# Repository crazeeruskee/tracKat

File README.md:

# tracKat
A Distributed BLE Sensor Network For Tracking Pet Eating Habits

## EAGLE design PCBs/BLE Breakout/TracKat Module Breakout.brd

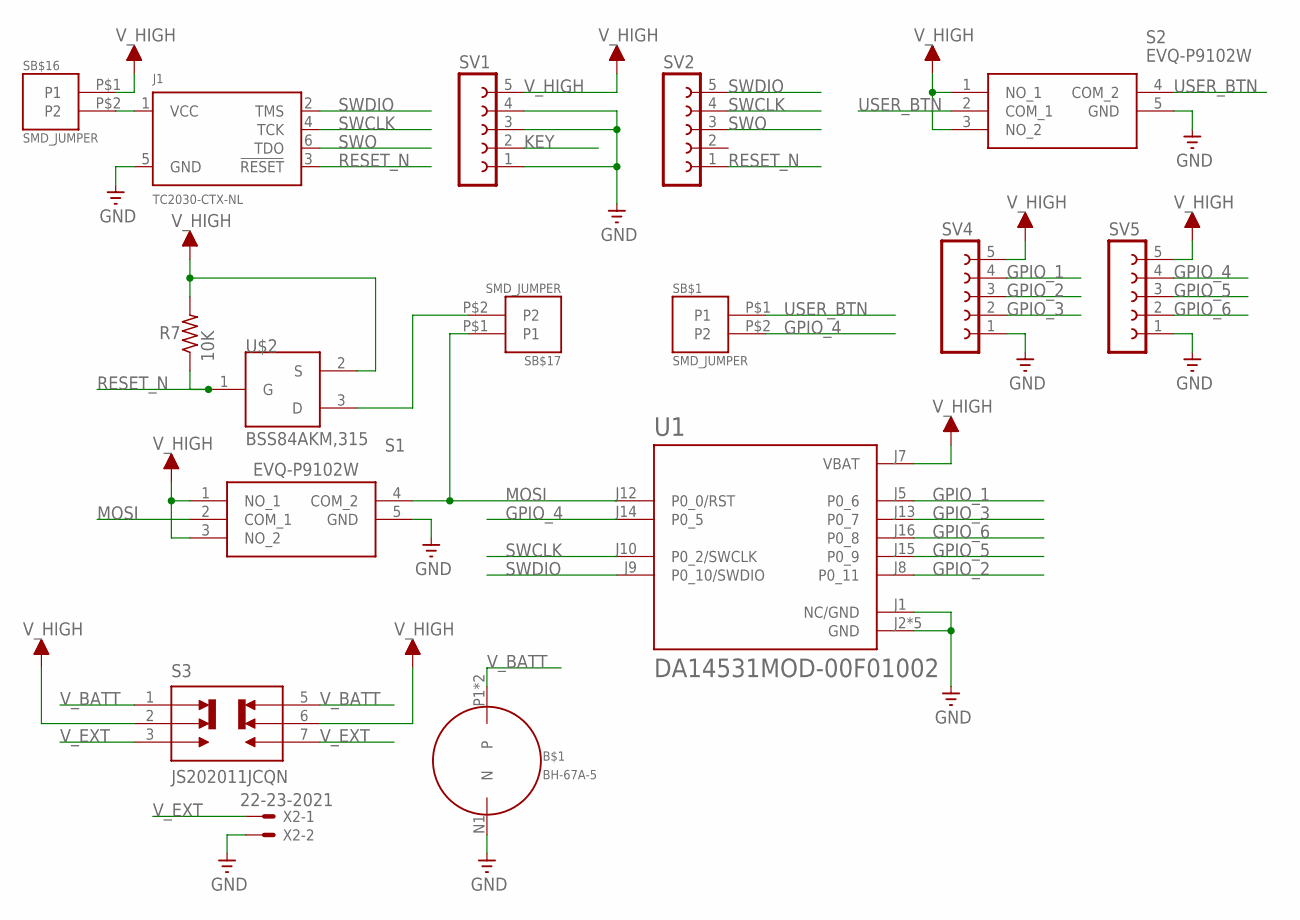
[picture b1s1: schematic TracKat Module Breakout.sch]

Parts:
B$1: BH-67A-5
J1: TC2030-CTX-NL; TC2030-IDC-NL
R7: 10K; R0603
S1, S2: EVQ-P9102W; EVQP9102W
S3: JS202011JCQN; SW_JS202011JCQN
SB$1, SB$16, SB$17: SMD_JUMPER
SV1, SV2, SV4, SV5: FE05-1
U1: DA14531MOD-00F01002; XCVR_DA14531MOD-00F01002
U$2: BSS84AKM,315; DFN985X585X50-3N
X2: 22-23-2021

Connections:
GND: B$1.N1 (N), J1.5 (GND), S1.5 (GND), S2.5 (GND), SV4.1, SV5.1, U1.J1 (NC/GND), U1.J2 (GND), U1.J3 (GND), U1.J4 (GND), U1.J6 (GND), U1.J11 (GND), X2.2
GPIO_1: SV4.4, U1.J5 (P0_6)
GPIO_2: SV4.3, U1.J8 (P0_11)
GPIO_3: SV4.2, U1.J13 (P0_7)
GPIO_4: SB$1.P$2 (P2), SV5.4, U1.J14 (P0_5)
GPIO_5: SV5.3, U1.J15 (P0_9)
GPIO_6: SV5.2, U1.J16 (P0_8)
KEY: SV1.2
MOSI: S1.2 (COM_1), S1.4 (COM_2), SB$17.P$1 (P1), U1.J12 (P0_0/RST)
unnamed: SV1.1, SV1.3, SV1.4
unnamed: J1.1 (VCC), SB$16.P$2 (P2)
unnamed: SB$17.P$2 (P2), U$2.3 (D)
RESET_N: J1.3 (!RESET), R7.1, SV2.1, U$2.1 (G)
SWCLK: J1.4 (TCK), SV2.4, U1.J10 (P0_2/SWCLK)
SWDIO: J1.2 (TMS), SV2.5, U1.J9 (P0_10/SWDIO)
SWO: J1.6 (TDO), SV2.3
USER_BTN: S2.2 (COM_1), S2.4 (COM_2), SB$1.P$1 (P1)
V_BATT: B$1.P1, B$1.P2, S3.1, S3.5
V_EXT: S3.3, S3.7, X2.1
V_HIGH: R7.2, S1.1 (NO_1), S1.3 (NO_2), S2.1 (NO_1), S2.3 (NO_2), S3.2, S3.6, SB$16.P$1 (P1), SV1.5, SV4.5, SV5.5, U1.J7 (VBAT), U$2.2 (S)

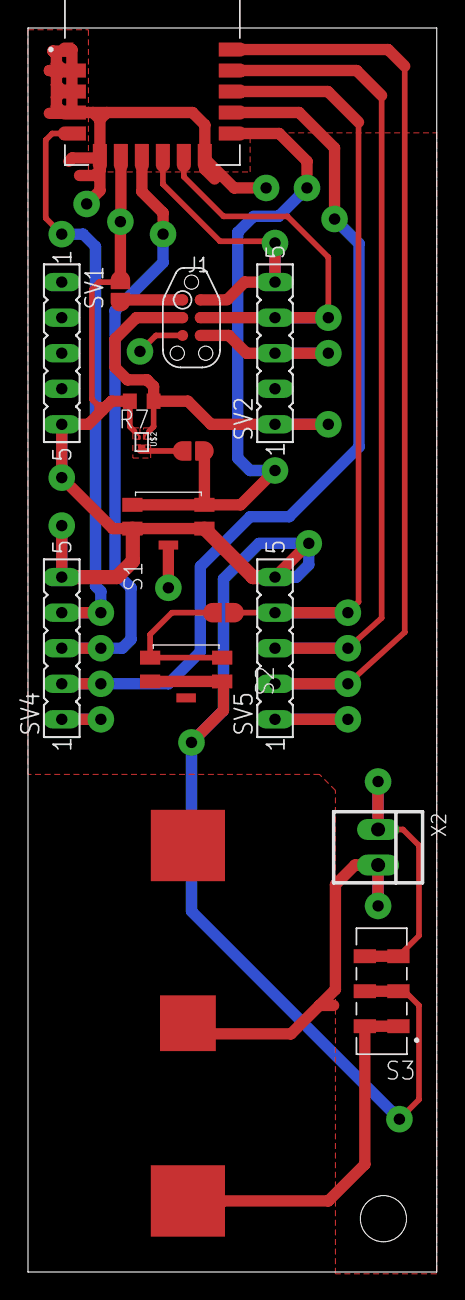
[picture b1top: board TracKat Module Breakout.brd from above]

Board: 2 copper layers, 29.2 x 88.9 mm, 16 parts (0 on the bottom side), 19 nets.

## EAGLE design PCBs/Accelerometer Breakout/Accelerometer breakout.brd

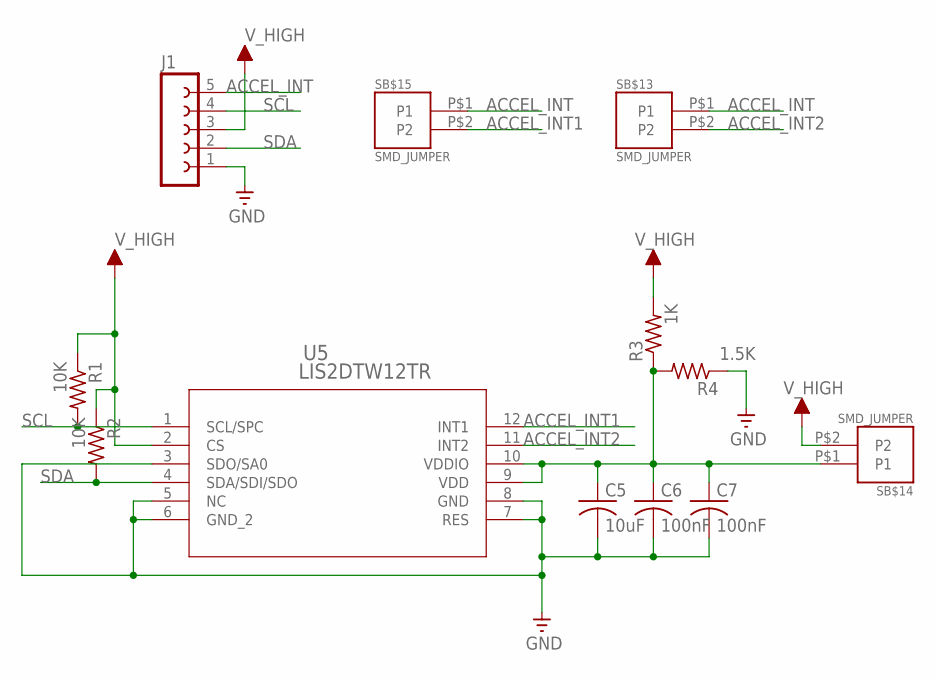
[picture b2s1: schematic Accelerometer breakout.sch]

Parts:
C5: 10uF; C0603
C6, C7: 100nF; C0603
J1: FE05-1
R1, R2: 10K; R0603
R3: 1K; R0603
R4: 1.5K; R0603
SB$13, SB$14, SB$15: SMD_JUMPER
U5: LIS2DTW12TR; LGA_DTW12_STM

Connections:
ACCEL_INT: J1.5, SB$13.P$1 (P1), SB$15.P$1 (P1)
ACCEL_INT1: SB$15.P$2 (P2), U5.12 (INT1)
ACCEL_INT2: SB$13.P$2 (P2), U5.11 (INT2)
GND: C5.2, C6.2, C7.2, J1.1, R4.1, U5.3 (SDO/SA0), U5.5 (NC), U5.6 (GND_2), U5.7 (RES), U5.8 (GND)
unnamed: C5.1, C6.1, C7.1, R3.1, R4.2, SB$14.P$1 (P1), U5.9 (VDD), U5.10 (VDDIO)
SCL: J1.4, R1.2, U5.1 (SCL/SPC)
SDA: J1.2, R2.2, U5.4 (SDA/SDI/SDO)
V_HIGH: J1.3, R1.1, R2.1, R3.2, SB$14.P$2 (P2), U5.2 (CS)

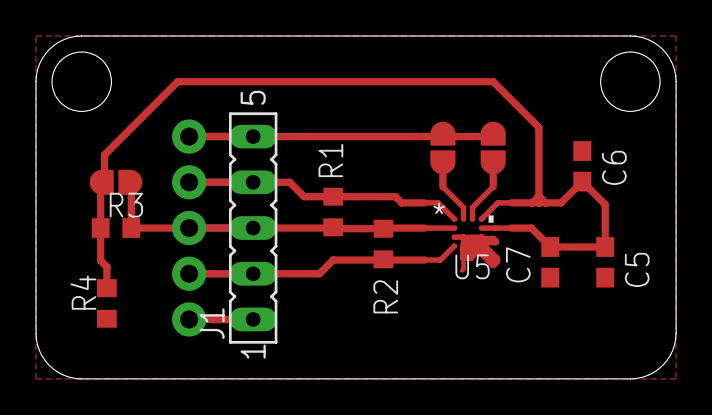
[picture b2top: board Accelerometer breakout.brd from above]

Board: 2 copper layers, 35.6 x 19.1 mm, 12 parts (0 on the bottom side), 8 nets.

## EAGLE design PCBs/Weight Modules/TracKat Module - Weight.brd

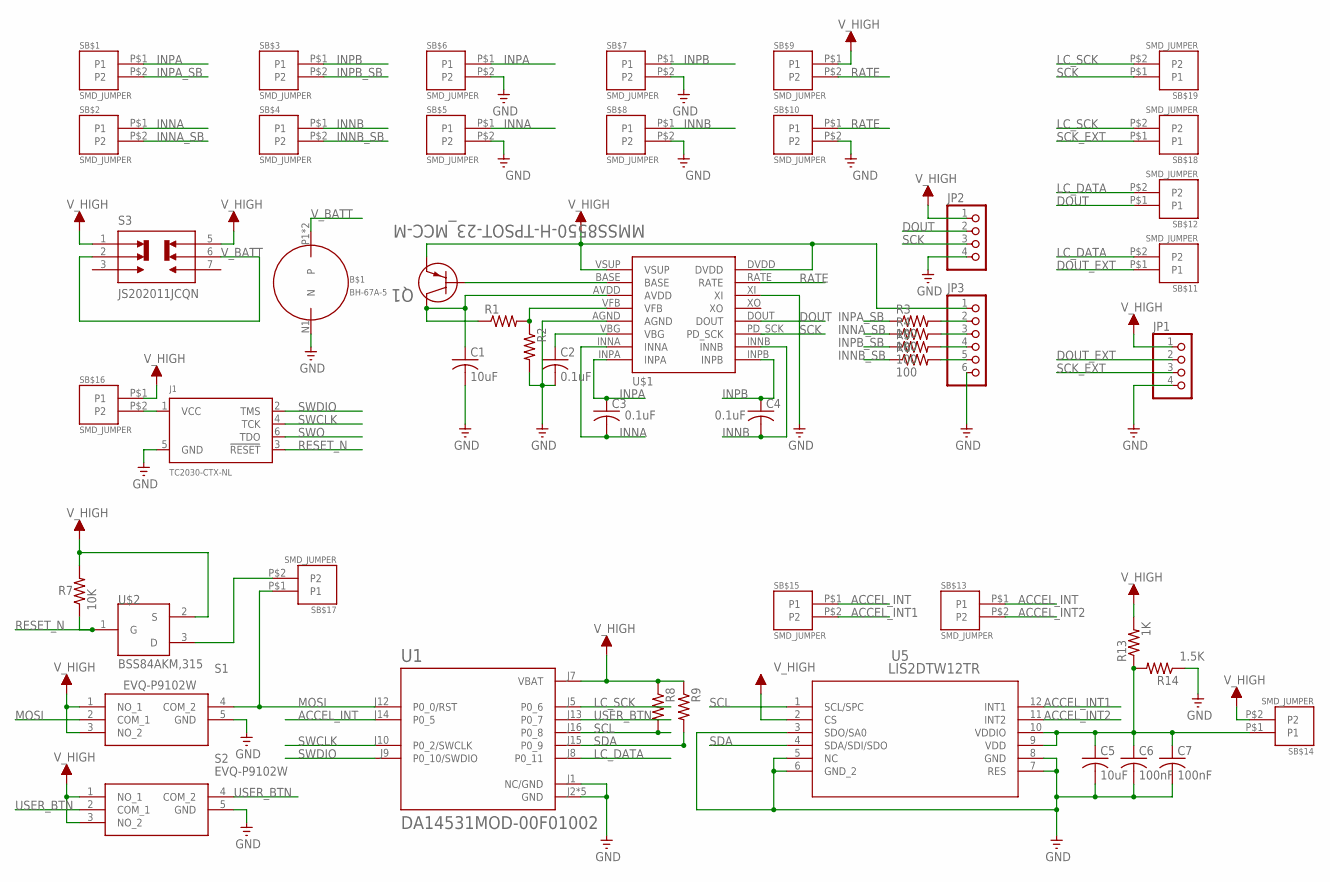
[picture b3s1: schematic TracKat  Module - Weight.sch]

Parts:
B$1: BH-67A-5
C1, C5: 10uF; C0603
C2, C3, C4: 0.1uF; C0603
C6, C7: 100nF; C0603
J1: TC2030-CTX-NL; TC2030-IDC-NL
JP1, JP2: PINHD-1X4; 1X04
JP3: PINHD-1X6; 1X06
Q1: MMSS8550-H-TPSOT-23_MCC-M; SOT-23_MCC-M
R1, R2, R8, R9: R-US_R0603; R0603
R3, R4, R5, R6: 100; R0603
R7: 10K; R0603
R13: 1K; R0603
R14: 1.5K; R0603
S1, S2: EVQ-P9102W; EVQP9102W
S3: JS202011JCQN; SW_JS202011JCQN
SB$1, SB$2, SB$3, SB$4, SB$5, SB$6, SB$7, SB$8, SB$9, SB$10, SB$11, SB$12, SB$13, SB$14, SB$15, SB$16, SB$17, SB$18, SB$19: SMD_JUMPER
U1: DA14531MOD-00F01002; XCVR_DA14531MOD-00F01002
U5: LIS2DTW12TR; LGA_DTW12_STM
U$1: HX711
U$2: BSS84AKM,315; DFN985X585X50-3N

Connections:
ACCEL_INT: SB$13.P$1 (P1), SB$15.P$1 (P1), U1.J14 (P0_5)
ACCEL_INT1: SB$15.P$2 (P2), U5.12 (INT1)
ACCEL_INT2: SB$13.P$2 (P2), U5.11 (INT2)
DOUT: JP2.2, SB$12.P$1 (P1), U$1.DOUT
DOUT_EXT: JP1.2, SB$11.P$1 (P1)
GND: B$1.N1 (N), C1.2, C2.2, C5.2, C6.2, C7.2, J1.5 (GND), JP1.4, JP2.4, JP3.6, R2.2, R14.1, S1.5 (GND), S2.5 (GND), SB$5.P$2 (P2), SB$6.P$2 (P2), SB$7.P$2 (P2), SB$8.P$2 (P2), SB$10.P$2 (P2), U1.J1 (NC/GND), U1.J2 (GND), U1.J3 (GND), U1.J4 (GND), U1.J6 (GND), U1.J11 (GND), U5.3 (SDO/SA0), U5.5 (NC), U5.6 (GND_2), U5.7 (RES), U5.8 (GND), U$1.AGND, U$1.XI
INNA: C3.2, SB$2.P$1 (P1), SB$5.P$1 (P1), U$1.INNA
INNA_SB: R4.1, SB$2.P$2 (P2)
INNB: C4.2, SB$4.P$1 (P1), SB$8.P$1 (P1), U$1.INNB
INNB_SB: R6.1, SB$4.P$2 (P2)
INPA: C3.1, SB$1.P$1 (P1), SB$6.P$1 (P1), U$1.INPA
INPA_SB: R3.1, SB$1.P$2 (P2)
INPB: C4.1, SB$3.P$1 (P1), SB$7.P$1 (P1), U$1.INPB
INPB_SB: R5.1, SB$3.P$2 (P2)
LC_DATA: SB$11.P$2 (P2), SB$12.P$2 (P2), U1.J8 (P0_11)
LC_SCK: SB$18.P$2 (P2), SB$19.P$2 (P2), U1.J5 (P0_6)
MOSI: S1.2 (COM_1), S1.4 (COM_2), SB$17.P$1 (P1), U1.J12 (P0_0/RST)
unnamed: R1.2, R2.1, U$1.VFB
unnamed: Q1.1, U$1.BASE
unnamed: C1.1, Q1.3, R1.1, U$1.AVDD
unnamed: C2.1, U$1.VBG
unnamed: JP3.5, R6.2
unnamed: JP3.4, R5.2
unnamed: JP3.3, R4.2
unnamed: JP3.2, R3.2
unnamed: C5.1, C6.1, C7.1, R13.1, R14.2, SB$14.P$1 (P1), U5.9 (VDD), U5.10 (VDDIO)
unnamed: J1.1 (VCC), SB$16.P$2 (P2)
unnamed: SB$17.P$2 (P2), U$2.3 (D)
RATE: SB$9.P$2 (P2), SB$10.P$1 (P1), U$1.RATE
RESET_N: J1.3 (!RESET), R7.1, U$2.1 (G)
SCK: JP2.3, SB$19.P$1 (P1), U$1.PD_SCK
SCK_EXT: JP1.3, SB$18.P$1 (P1)
SCL: R8.2, U1.J16 (P0_8), U5.1 (SCL/SPC)
SDA: R9.2, U1.J15 (P0_9), U5.4 (SDA/SDI/SDO)
SWCLK: J1.4 (TCK), U1.J10 (P0_2/SWCLK)
SWDIO: J1.2 (TMS), U1.J9 (P0_10/SWDIO)
SWO: J1.6 (TDO)
USER_BTN: S2.2 (COM_1), S2.4 (COM_2), U1.J13 (P0_7)
V_BATT: B$1.P1, B$1.P2, S3.2, S3.6
V_HIGH: JP1.1, JP2.1, JP3.1, Q1.2, R7.2, R8.1, R9.1, R13.2, S1.1 (NO_1), S1.3 (NO_2), S2.1 (NO_1), S2.3 (NO_2), S3.1, S3.5, SB$9.P$1 (P1), SB$14.P$2 (P2), SB$16.P$1 (P1), U1.J7 (VBAT), U5.2 (CS), U$1.DVDD, U$1.VSUP, U$2.2 (S)

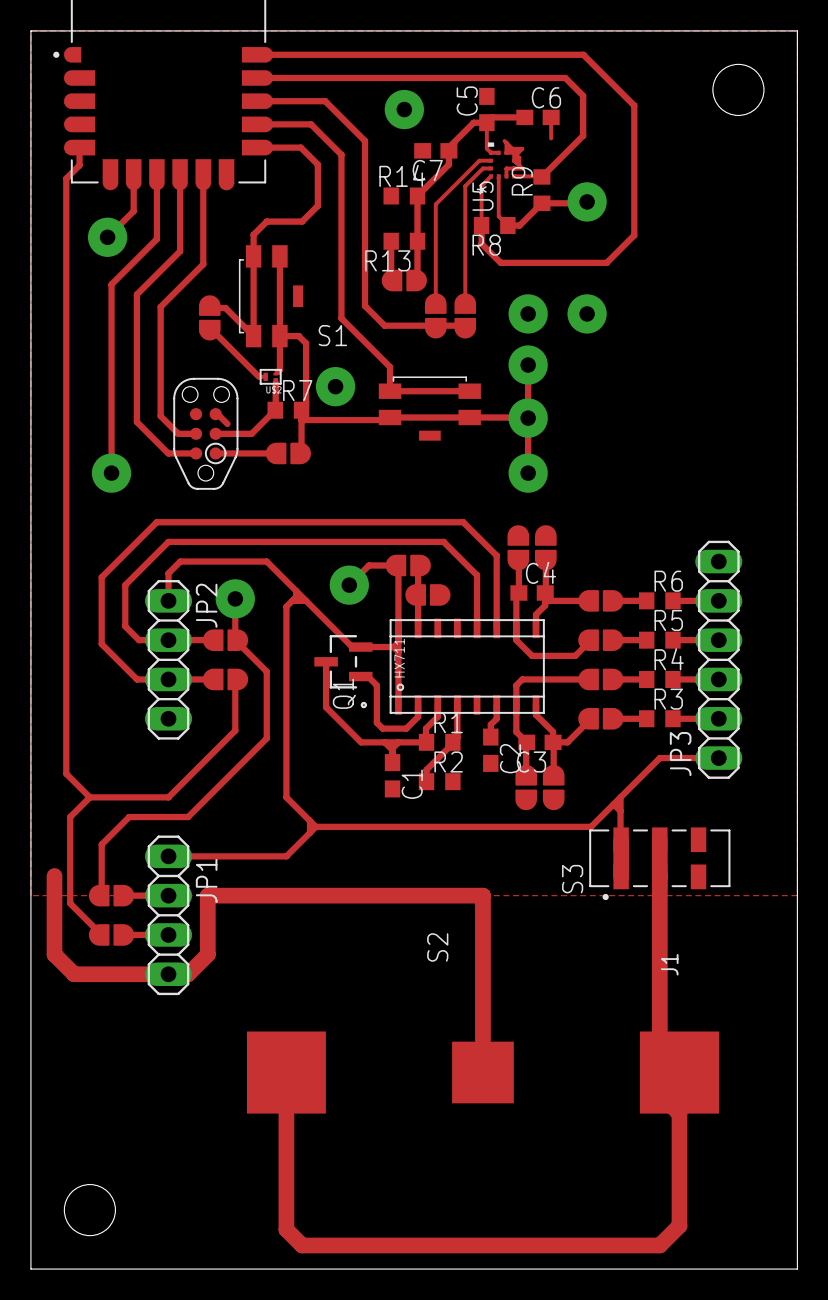
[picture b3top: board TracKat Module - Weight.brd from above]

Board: 2 copper layers, 49.5 x 80.0 mm, 50 parts (0 on the bottom side), 39 nets.

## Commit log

2021-12-06 Initial Project Commit
2021-12-06 Add USB Dev Kit configuration option
    Load Cell Tag project used to only work for custom tag PCB because of different GPIO and related functions. This commit adds a configuration macro to select between the custom tag and the COTS USB De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
2021-12-08 Initial Weight Tag (V1) PCB Commit
2021-12-09 Add Load Cell structure, remove global variables
2021-12-10 Initial Accelerometer Breakout Commit
2021-12-10 Create PCBs Directory
2021-12-10 Move Weight Module brd file into new directory
2021-12-10 Move Weight Module sch file into new directory
2021-12-10 Move Weight Module sch file to correct directory
2021-12-10 Move Accelerometer brd file to new directory
2021-12-10 Move Accelerometer sch file to new directory
2021-12-10 Add Initial BLE Module Breakout Board files
2021-12-10 Move file to correct directory
2021-12-10 Add BLE Breakout board image
2021-12-10 Add timestamping, number of values reporting, and button value test
2021-12-12 Add baseline value reporting, revert to non struct based load cell driving
2021-12-12 Improve routing and copper pour isolation
    This design is fully functional but still has two errors: 1) SWD V_ref is placed on bottom pin of top left header - this should be routed to top pin instead 2) Middle and lower copper pours on bottom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
2021-12-12 Improve routing and copper pours
    This design is fully functional but still has two errors: 1) SWD V_ref is placed on bottom pin of top left header - this should be routed to top pin instead 2) Middle and lower copper pours on bottom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
2021-12-12 Add CUSTOM_TAG2 configuration option for custom dev board gpio
2021-12-12 Improve weight value thresholding and introduce automatic bowl refill tracking; fix bugs with time tracking; report weight and timestamps as arrays and clear after each read
2021-12-12 Implement button based RFID array reporting
2021-12-24 Finalize build for demo release

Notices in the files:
parts and their libraries:
COPYRIGHT: Copyright (C) 2021 Ultra Librarian. All rights reserved.
